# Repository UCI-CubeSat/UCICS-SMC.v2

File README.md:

# UCI CubeSat OBC v2
### Made by UCI Avionics

These design files are for the System Management Controller and Communication Subsystem of the UCI CubeSat.  
They are NOT final and are subject to change and modifications.  

Verification and finalization pending.  

Features:
- STM32F412ZG microcontroller for SMC
- 2 STM32L431RCT6 microcontrollers for communications controllers
- RF MUX and CPLD switching logic for communications failover
- AX5043 communications transceiver over SPI bus
- TCAN1042 CAN transceiver
- 4 magnetorquer PWM outputs
- 2 BMX160 interial measurement units
- CPLD error detection and handling
- 12 sun sensor ADC ports
- System and magnetorquer current monitoring via INA226 shunt resistor I2C current sensors
- External application connector

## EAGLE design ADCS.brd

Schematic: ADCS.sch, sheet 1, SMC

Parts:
C27, C28, C33, C34, C35, C36, C37, C38, C39, C40, C41, C42, C43, C44, C45, C46, C47, C48, C68, C69, C70, C71, C72, C73, C74, C75, C76, C80, C81, C82, C83, C84, C93, C94, C95, C96, C98, C99, C100, C101, C102, C103, C104, C105, C106, C107, C108, C109, C110, C111: 0.1uF; 0402
C29, C85, C86, C87, C112, C113, C114: 1uF; 0402
C88, C91, C92, C97: 2.2uF; 0402
C89, C115, C116: 4.7uF; 0603
C90, C117: 10uF; 0603
C118, C119: 10nF; 0603
C120, C121, C122, C123: 22uF; 0603
C143, C144, C145, C146, C147, C148, C149, C150, C151, C152, C153, C154, C155, C156, C172, C174: 0.1uF; 0603
C171, C173: 1uF; 0603
JP1, JP4: PINHD-1X8; 1X08
JP9: PINHD-1X4; 1X04
R3: 56R_10%; 0402
R4, R36, R38: 4.7k; 0603
R9, R40, R62, R63: 10k; 0603
R10, R12: 2.2k; 0603
R37, R39: DNI; 0603
R41: 120R; 0603
R72: 100k; 0603
U2: Value; ZWT0337A-IPC_A
U14: Value; TEXAS_INSTRUMENTS-CAN_TRANSCEIVER-TCAN1042/LED_DRIVER-TLC59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
X4: 2510-; PAK100/2500-10
Y2: 20MHz; ESC-OSCILLATOR-ECS_200_9_33B_CTP_TR

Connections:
!COMMS1_UNRESPONSIVE_FROM_SMC: R62.2, U2.F2 (GPIO20); also elsewhere on the board
!COMMS2_UNRESPONSIVE_FROM_SMC: R63.2, U2.F3 (GPIO21); also elsewhere on the board
!GLOBAL_RESET: C118.1, R4.2, U2.F19 (XRS_N); also elsewhere on the board
!MTQ_12_FAULT: U2.C11 (GPIO86); also elsewhere on the board
!MTQ_12_SLEEP: U2.B11 (GPIO85); also elsewhere on the board
!MTQ_34_FAULT: U2.D6 (GPIO89); also elsewhere on the board
!MTQ_34_SLEEP: U2.C6 (GPIO88); also elsewhere on the board
!SDRAM_CAS: U2.K4 (GPIO23); also elsewhere on the board
!SDRAM_CS: U2.U13 (GPIO32); also elsewhere on the board
!SDRAM_RAS: U2.J4 (GPIO22); also elsewhere on the board
!SDRAM_WE: U2.U11 (GPIO31); also elsewhere on the board
!SMC_NAND_CS: U2.E4 (GPIO19); also elsewhere on the board
!SMC_TRST: C119.1, R10.1, U2.V14 (TRST_N), X4.10
!TPS53513_PGOOD: R72.2; also elsewhere on the board
ADC_A0: C149.1, JP1.2, U2.U1 (ADCINA0_DACOUTA)
ADC_A1: C148.1, JP1.3, U2.T1 (ADCINA1_DACOUTB)
ADC_A2: C147.1, JP1.4, U2.U2 (ADCINA2_CMPIN1P)
ADC_A3: C146.1, JP1.5, U2.T2 (ADCINA3_CMPIN1N)
ADC_A4: C145.1, JP1.6, U2.U3 (ADCINA4_CMPIN2P)
ADC_A5: C144.1, JP1.7, U2.T3 (ADCINA5_CMPIN2N)
ADC_B0: C156.1, JP4.2, U2.V2 (ADCINB0_VDAC)
ADC_B1: C155.1, JP4.3, U2.W2 (ADCINB1_DACOUTC)
ADC_B2: C154.1, JP4.4, U2.V3 (ADCINB2_CMPIN3P)
ADC_B3: C153.1, JP4.5, U2.W3 (ADCINB3_CMPIN3N)
ADC_B4: C152.1, JP4.6, U2.V4 (ADCINB4)
ADC_B5: C151.1, JP4.7, U2.W4 (ADCINB5)
BMX160_1_INT1: U2.C1 (GPIO11); also elsewhere on the board
BMX160_1_INT2: U2.C2 (GPIO12); also elsewhere on the board
BMX160_2_INT1: U2.D1 (GPIO13); also elsewhere on the board
BMX160_2_INT2: U2.D2 (GPIO14); also elsewhere on the board
CANH: R41.1, U14.7 (CANH); also elsewhere on the board
CANL: R41.2, U14.6 (CANL); also elsewhere on the board
EPWM1A: U2.C8 (GPIO0); also elsewhere on the board
EPWM1B: U2.D8 (GPIO1); also elsewhere on the board
EPWM2A: U2.A7 (GPIO2); also elsewhere on the board
EPWM2B: U2.B7 (GPIO3); also elsewhere on the board
EPWM3A: U2.C7 (GPIO4); also elsewhere on the board
EPWM3B: U2.D7 (GPIO5); also elsewhere on the board
EPWM4A: U2.A6 (GPIO6); also elsewhere on the board
EPWM4B: U2.B6 (GPIO7); also elsewhere on the board
MAIN_CURRENT_ALERT: U2.D3 (GPIO15); also elsewhere on the board
MTQ_12_ALERT: U2.A11 (GPIO84); also elsewhere on the board
MTQ_34_ALERT: U2.D11 (GPIO87); also elsewhere on the board
unnamed: U2.J19 (X2), Y2.1 (XI)
unnamed: U2.G19 (X1), Y2.3 (XO)
unnamed: R72.1, U2.C14 (GPIO83)
SDRAM_A0: U2.T14 (GPIO35); also elsewhere on the board
SDRAM_A1: U2.V16 (GPIO36); also elsewhere on the board
SDRAM_A2: U2.U16 (GPIO37); also elsewhere on the board
SDRAM_A3: U2.T16 (GPIO38); also elsewhere on the board
SDRAM_A4: U2.W17 (GPIO39); also elsewhere on the board
SDRAM_A5: U2.K19 (GPIO45); also elsewhere on the board
SDRAM_A6: U2.E19 (GPIO46); also elsewhere on the board
SDRAM_A7: U2.E18 (GPIO47); also elsewhere on the board
SDRAM_A8: U2.R16 (GPIO48); also elsewhere on the board
SDRAM_A9: U2.R17 (GPIO49); also elsewhere on the board
SDRAM_A10: U2.R18 (GPIO50); also elsewhere on the board
SDRAM_A11: U2.R19 (GPIO51); also elsewhere on the board
SDRAM_A12: U2.P16 (GPIO52); also elsewhere on the board
SDRAM_BA0: U2.T13 (GPIO33); also elsewhere on the board
SDRAM_BA1: U2.U14 (GPIO34); also elsewhere on the board
SDRAM_CKE: U2.W11 (GPIO29); also elsewhere on the board
SDRAM_CLK: U2.T11 (GPIO30); also elsewhere on the board
SDRAM_D0: U2.P19 (GPIO55); also elsewhere on the board
SDRAM_D1: U2.N16 (GPIO56); also elsewhere on the board
SDRAM_D2: U2.N18 (GPIO57); also elsewhere on the board
SDRAM_D3: U2.N17 (GPIO58); also elsewhere on the board
SDRAM_D4: U2.M16 (GPIO59); also elsewhere on the board
SDRAM_D5: U2.M17 (GPIO60); also elsewhere on the board
SDRAM_D6: U2.L16 (GPIO61); also elsewhere on the board
SDRAM_D7: U2.J17 (GPIO62); also elsewhere on the board
SDRAM_D8: U2.C16 (GPIO76); also elsewhere on the board
SDRAM_D9: U2.D16 (GPIO75); also elsewhere on the board
SDRAM_D10: U2.C17 (GPIO74); also elsewhere on the board
SDRAM_D11: U2.A16 (GPIO73); also elsewhere on the board
SDRAM_D12: U2.B16 (GPIO72); also elsewhere on the board
SDRAM_D13: U2.B17 (GPIO71); also elsewhere on the board
SDRAM_D14: U2.A17 (GPIO70); also elsewhere on the board
SDRAM_D15: U2.B18 (GPIO69); also elsewhere on the board
SDRAM_DQM0: U2.K3 (GPIO24); also elsewhere on the board
SDRAM_DQM1: U2.K2 (GPIO25); also elsewhere on the board
SMC_ERR_OUT: R9.1, U2.U19 (ERRORSTS); also elsewhere on the board
SMC_I2C0_SCL: R37.2, U2.J3 (GPIO105); also elsewhere on the board
SMC_I2C0_SDA: R36.2, U2.J2 (GPIO104); also elsewhere on the board
SMC_I2C1_SCL: R39.2, U2.U17 (GPIO41); also elsewhere on the board
SMC_I2C1_SDA: R38.2, U2.V17 (GPIO40); also elsewhere on the board
SMC_MCAN_RX: U2.B2 (GPIO10), U14.4 (RXD)
SMC_MCAN_STB: R40.1, U2.G3 (GPIO9), U14.8 (STB)
SMC_MCAN_TX: U2.G2 (GPIO8), U14.1 (TXD)
SMC_NAND_MISO: U2.E2 (GPIO17); also elsewhere on the board
SMC_NAND_MOSI: U2.E1 (GPIO16); also elsewhere on the board
SMC_NAND_SCK: U2.E3 (GPIO18); also elsewhere on the board
SMC_TCK: U2.V15 (TCK), X4.4
SMC_TDI: U2.W13 (TDI), X4.8
SMC_TDO: U2.W15 (TDO), X4.6
SMC_TMS: R12.2, U2.W14 (TMS), X4.2
SMC_UART0_RX: JP9.3, U2.C19 (GPIO43); also elsewhere on the board
SMC_UART0_TX: JP9.2, U2.D19 (GPIO42); also elsewhere on the board
VCC_3V3_IO: C27.1, C28.1, C29.1, C33.1, C34.1, C35.1, C36.1, C37.1, C38.1, C39.1, C40.1, C41.1, C42.1, C43.1, C44.1, C45.1, C46.1, C47.1, C48.1, C68.1, C69.1, C70.1, C71.1, C72.1, C73.1, C74.1, C75.1, C76.1, C80.1, C81.1, C82.1, C83.1, C84.1, C85.1, C86.1, C87.1, C88.1, C89.1, C90.1, C91.1, C92.1, C93.1, C94.1, C95.1, C96.1, C97.1, C120.1, C121.1, C122.1, C123.1, C143.1, C150.1, C171.1, C172.1, JP1.1, JP4.1, JP9.1, R4.1, R12.1, R36.1, R37.1, R38.1, R39.1, R62.1, R63.1, U2.A9 (VDDIO_2), U2.A18 (VDDIO_3), U2.B1 (VDDIO_4), U2.E7 (VDDIO_5), U2.E10 (VDDIO_6), U2.E13 (VDDIO_7), U2.E16 (VDDIO_8), U2.F4 (VDDIO_9), U2.F7 (VDDIO_10), U2.F10 (VDDIO_11), U2.F13 (VDDIO_12), U2.F16 (VDDIO_13), U2.G4 (VDDIO_14), U2.G5 (VDDIO_15), U2.G6 (VDDIO_16), U2.H5 (VDDIO_17), U2.H6 (VDDIO_18), U2.H16 (VDDOSC_2), U2.H17 (VDDOSC), U2.L14 (VDDIO_19), U2.L15 (VDDIO_20), U2.M1 (VDDIO_21), U2.M5 (VDDIO_22), U2.M6 (VDDIO_23), U2.N14 (VDDIO_24), U2.N15 (VDDIO_25), U2.P6 (VDDA_2), U2.P9 (VDDIO_26), U2.R1 (VREFHIC), U2.R6 (VDDA), U2.R9 (VDDIO_27), U2.R11 (VDD3VFL_2), U2.R12 (VDD3VFL), U2.V1 (VREFHIA), U2.V5 (VREFHID), U2.V19 (VDDIO_28), U2.W5 (VREFHIB), U2.W8 (VDDIO), U14.5 (VIO), X4.1; also elsewhere on the board
VCC_5V0: C173.1, C174.1, U14.3 (VCC); also elsewhere on the board
VDD_CORE: C98.1, C99.1, C100.1, C101.1, C102.1, C103.1, C104.1, C105.1, C106.1, C107.1, C108.1, C109.1, C110.1, C111.1, C112.1, C113.1, C114.1, C115.1, C116.1, C117.1, R3.1, U2.E9 (VDD_2), U2.E11 (VDD_3), U2.F9 (VDD_4), U2.F11 (VDD_5), U2.G14 (VDD_6), U2.G15 (VDD_7), U2.J14 (VDD_8), U2.J15 (VDD_9), U2.K5 (VDD_10), U2.K6 (VDD_11), U2.P10 (VDD_12), U2.P13 (VDD_13), U2.R10 (VDD_14), U2.R13 (VDD)
VSS: C27.2, C28.2, C29.2, C33.2, C34.2, C35.2, C36.2, C37.2, C38.2, C39.2, C40.2, C41.2, C42.2, C43.2, C44.2, C45.2, C46.2, C47.2, C48.2, C68.2, C69.2, C70.2, C71.2, C72.2, C73.2, C74.2, C75.2, C76.2, C80.2, C81.2, C82.2, C83.2, C84.2, C85.2, C86.2, C87.2, C88.2, C89.2, C90.2, C91.2, C92.2, C93.2, C94.2, C95.2, C96.2, C97.2, C98.2, C99.2, C100.2, C101.2, C102.2, C103.2, C104.2, C105.2, C106.2, C107.2, C108.2, C109.2, C110.2, C111.2, C112.2, C113.2, C114.2, C115.2, C116.2, C117.2, C118.2, C119.2, C120.2, C121.2, C122.2, C123.2, C143.2, C144.2, C145.2, C146.2, C147.2, C148.2, C149.2, C150.2, C151.2, C152.2, C153.2, C154.2, C155.2, C156.2, C171.2, C172.2, C173.2, C174.2, JP1.8, JP4.8, JP9.4, R3.2, R9.2, R10.2, R40.2, U2.A1 (VSS_2), U2.A10 (VSS_3), U2.A19 (VSS_4), U2.E5 (VSS_5), U2.E6 (VSS_6), U2.E8 (VSS_7), U2.E12 (VSS_8), U2.E14 (VSS_9), U2.E15 (VSS_10), U2.F5 (VSS_11), U2.F6 (VSS_12), U2.F8 (VSS_13), U2.F12 (VSS_14), U2.F14 (VSS_15), U2.F15 (VSS_16), U2.G16 (VSS_17), U2.G17 (VSS_18), U2.H8 (VSS_19), U2.H9 (VSS_20), U2.H10 (VSS_21), U2.H11 (VSS_22), U2.H12 (VSS_23), U2.H14 (VSS_24), U2.H15 (VSS_25), U2.H18 (VSSOSC_2), U2.H19 (VSSOSC), U2.J5 (VSS_26), U2.J6 (VSS_27), U2.J8 (VSS_28), U2.J9 (VSS_29), U2.J10 (VSS_30), U2.J11 (VSS_31), U2.J12 (VSS_32), U2.K8 (VSS_33), U2.K9 (VSS_34), U2.K10 (VSS_35), U2.K11 (VSS_36), U2.K12 (VSS_37), U2.K14 (VSS_38), U2.K15 (VSS_39), U2.L5 (VSS_40), U2.L6 (VSS_41), U2.L8 (VSS_42), U2.L9 (VSS_43), U2.L10 (VSS_44), U2.L11 (VSS_45), U2.L12 (VSS_46), U2.L18 (VSS_47), U2.M8 (VSS_48), U2.M9 (VSS_49), U2.M10 (VSS_50), U2.M11 (VSS_51), U2.M12 (VSS_52), U2.M14 (VSS_53), U2.M15 (VSS_54), U2.N1 (VSS_55), U2.N5 (VSS_56), U2.N6 (VSS_57), U2.P1 (VSSA_2), U2.P2 (VREFLOC), U2.P5 (VSSA_3), U2.P7 (VSS_58), U2.P8 (VSS_59), U2.P11 (VSS_60), U2.P12 (VSS_61), U2.P14 (VSS_62), U2.P15 (VSS_63), U2.R2 (VREFLOA), U2.R5 (VSSA_4), U2.R7 (VSS_64), U2.R8 (VSS_65), U2.R14 (VSS_66), U2.R15 (VSS_67), U2.V6 (VREFLOB), U2.V7 (VSSA_5), U2.W1 (VSSA), U2.W6 (VREFLOD), U2.W7 (VSS_68), U2.W19 (VSS), U14.2 (GND), X4.3, X4.5, X4.9, Y2.2 (VSS), Y2.4 (VSS); also elsewhere on the board

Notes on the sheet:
Ground block
VDD + Decaps
ADC block (sun sensor and auxiliary)
SMC control block

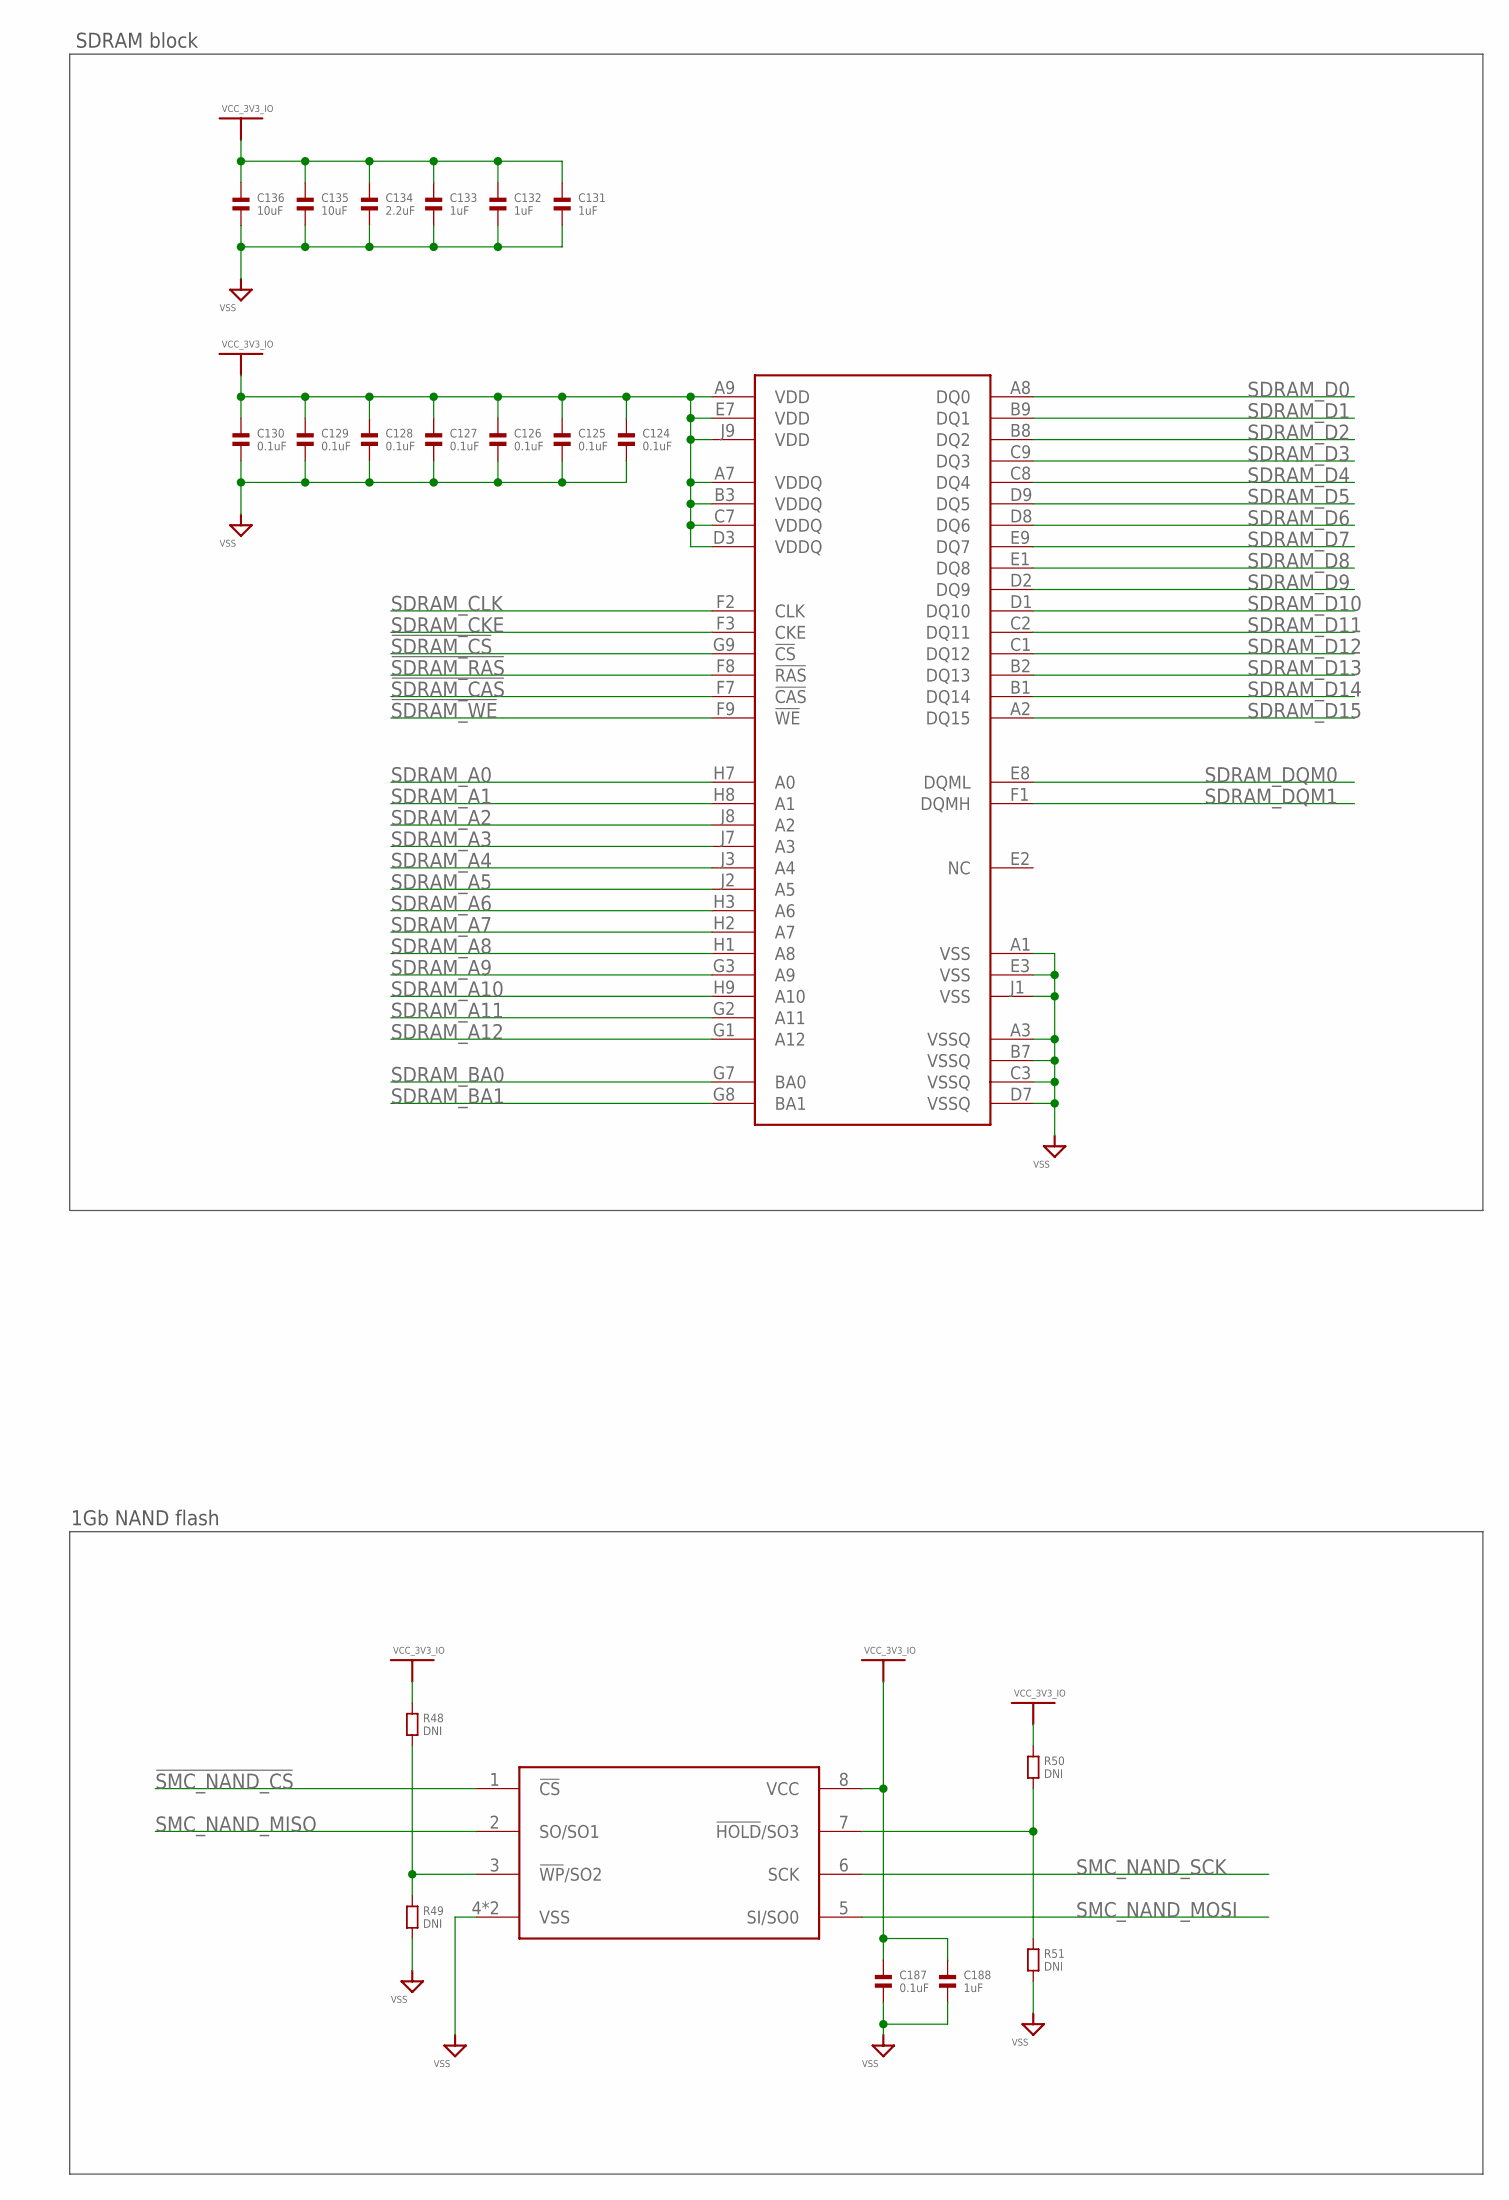
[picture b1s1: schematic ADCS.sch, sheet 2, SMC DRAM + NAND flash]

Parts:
C124, C125, C126, C127, C128, C129, C130, C187: 0.1uF; 0603
C131, C132, C133, C188: 1uF; 0603
C134: 2.2uF; 0603
C135, C136: 10uF; 0603
R48, R49, R50, R51: DNI; 0603
U6: ISSI-DRAM-IS42S16320F-7TL
U16: KIOXIA_AMERICA-NAND_FLASH-TC58CVG0S3HRAIG

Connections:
!SDRAM_CAS: U6.F7 (!CAS); also elsewhere on the board
!SDRAM_CS: U6.G9 (!CS); also elsewhere on the board
!SDRAM_RAS: U6.F8 (!RAS); also elsewhere on the board
!SDRAM_WE: U6.F9 (!WE); also elsewhere on the board
!SMC_NAND_CS: U16.1 (!CS); also elsewhere on the board
unnamed: R48.2, R49.1, U16.3 (!WP!/SO2)
unnamed: R50.2, R51.1, U16.7 (!HOLD!/SO3)
SDRAM_A0: U6.H7 (A0); also elsewhere on the board
SDRAM_A1: U6.H8 (A1); also elsewhere on the board
SDRAM_A2: U6.J8 (A2); also elsewhere on the board
SDRAM_A3: U6.J7 (A3); also elsewhere on the board
SDRAM_A4: U6.J3 (A4); also elsewhere on the board
SDRAM_A5: U6.J2 (A5); also elsewhere on the board
SDRAM_A6: U6.H3 (A6); also elsewhere on the board
SDRAM_A7: U6.H2 (A7); also elsewhere on the board
SDRAM_A8: U6.H1 (A8); also elsewhere on the board
SDRAM_A9: U6.G3 (A9); also elsewhere on the board
SDRAM_A10: U6.H9 (A10); also elsewhere on the board
SDRAM_A11: U6.G2 (A11); also elsewhere on the board
SDRAM_A12: U6.G1 (A12); also elsewhere on the board
SDRAM_BA0: U6.G7 (BA0); also elsewhere on the board
SDRAM_BA1: U6.G8 (BA1); also elsewhere on the board
SDRAM_CKE: U6.F3 (CKE); also elsewhere on the board
SDRAM_CLK: U6.F2 (CLK); also elsewhere on the board
SDRAM_D0: U6.A8 (DQ0); also elsewhere on the board
SDRAM_D1: U6.B9 (DQ1); also elsewhere on the board
SDRAM_D2: U6.B8 (DQ2); also elsewhere on the board
SDRAM_D3: U6.C9 (DQ3); also elsewhere on the board
SDRAM_D4: U6.C8 (DQ4); also elsewhere on the board
SDRAM_D5: U6.D9 (DQ5); also elsewhere on the board
SDRAM_D6: U6.D8 (DQ6); also elsewhere on the board
SDRAM_D7: U6.E9 (DQ7); also elsewhere on the board
SDRAM_D8: U6.E1 (DQ8); also elsewhere on the board
SDRAM_D9: U6.D2 (DQ9); also elsewhere on the board
SDRAM_D10: U6.D1 (DQ10); also elsewhere on the board
SDRAM_D11: U6.C2 (DQ11); also elsewhere on the board
SDRAM_D12: U6.C1 (DQ12); also elsewhere on the board
SDRAM_D13: U6.B2 (DQ13); also elsewhere on the board
SDRAM_D14: U6.B1 (DQ14); also elsewhere on the board
SDRAM_D15: U6.A2 (DQ15); also elsewhere on the board
SDRAM_DQM0: U6.E8 (DQML); also elsewhere on the board
SDRAM_DQM1: U6.F1 (DQMH); also elsewhere on the board
SMC_NAND_MISO: U16.2 (SO/SO1); also elsewhere on the board
SMC_NAND_MOSI: U16.5 (SI/SO0); also elsewhere on the board
SMC_NAND_SCK: U16.6 (SCK); also elsewhere on the board
VCC_3V3_IO: C124.1, C125.1, C126.1, C127.1, C128.1, C129.1, C130.1, C131.1, C132.1, C133.1, C134.1, C135.1, C136.1, C187.1, C188.1, R48.1, R50.1, U6.A7 (VDDQ), U6.A9 (VDD), U6.B3 (VDDQ), U6.C7 (VDDQ), U6.D3 (VDDQ), U6.E7 (VDD), U6.J9 (VDD), U16.8 (VCC); also elsewhere on the board
VSS: C124.2, C125.2, C126.2, C127.2, C128.2, C129.2, C130.2, C131.2, C132.2, C133.2, C134.2, C135.2, C136.2, C187.2, C188.2, R49.2, R51.2, U6.A1 (VSS), U6.A3 (VSSQ), U6.B7 (VSSQ), U6.C3 (VSSQ), U6.D7 (VSSQ), U6.E3 (VSS), U6.J1 (VSS), U16.4 (VSS), U16.9 (VSS); also elsewhere on the board

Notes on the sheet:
SDRAM block
1Gb NAND flash

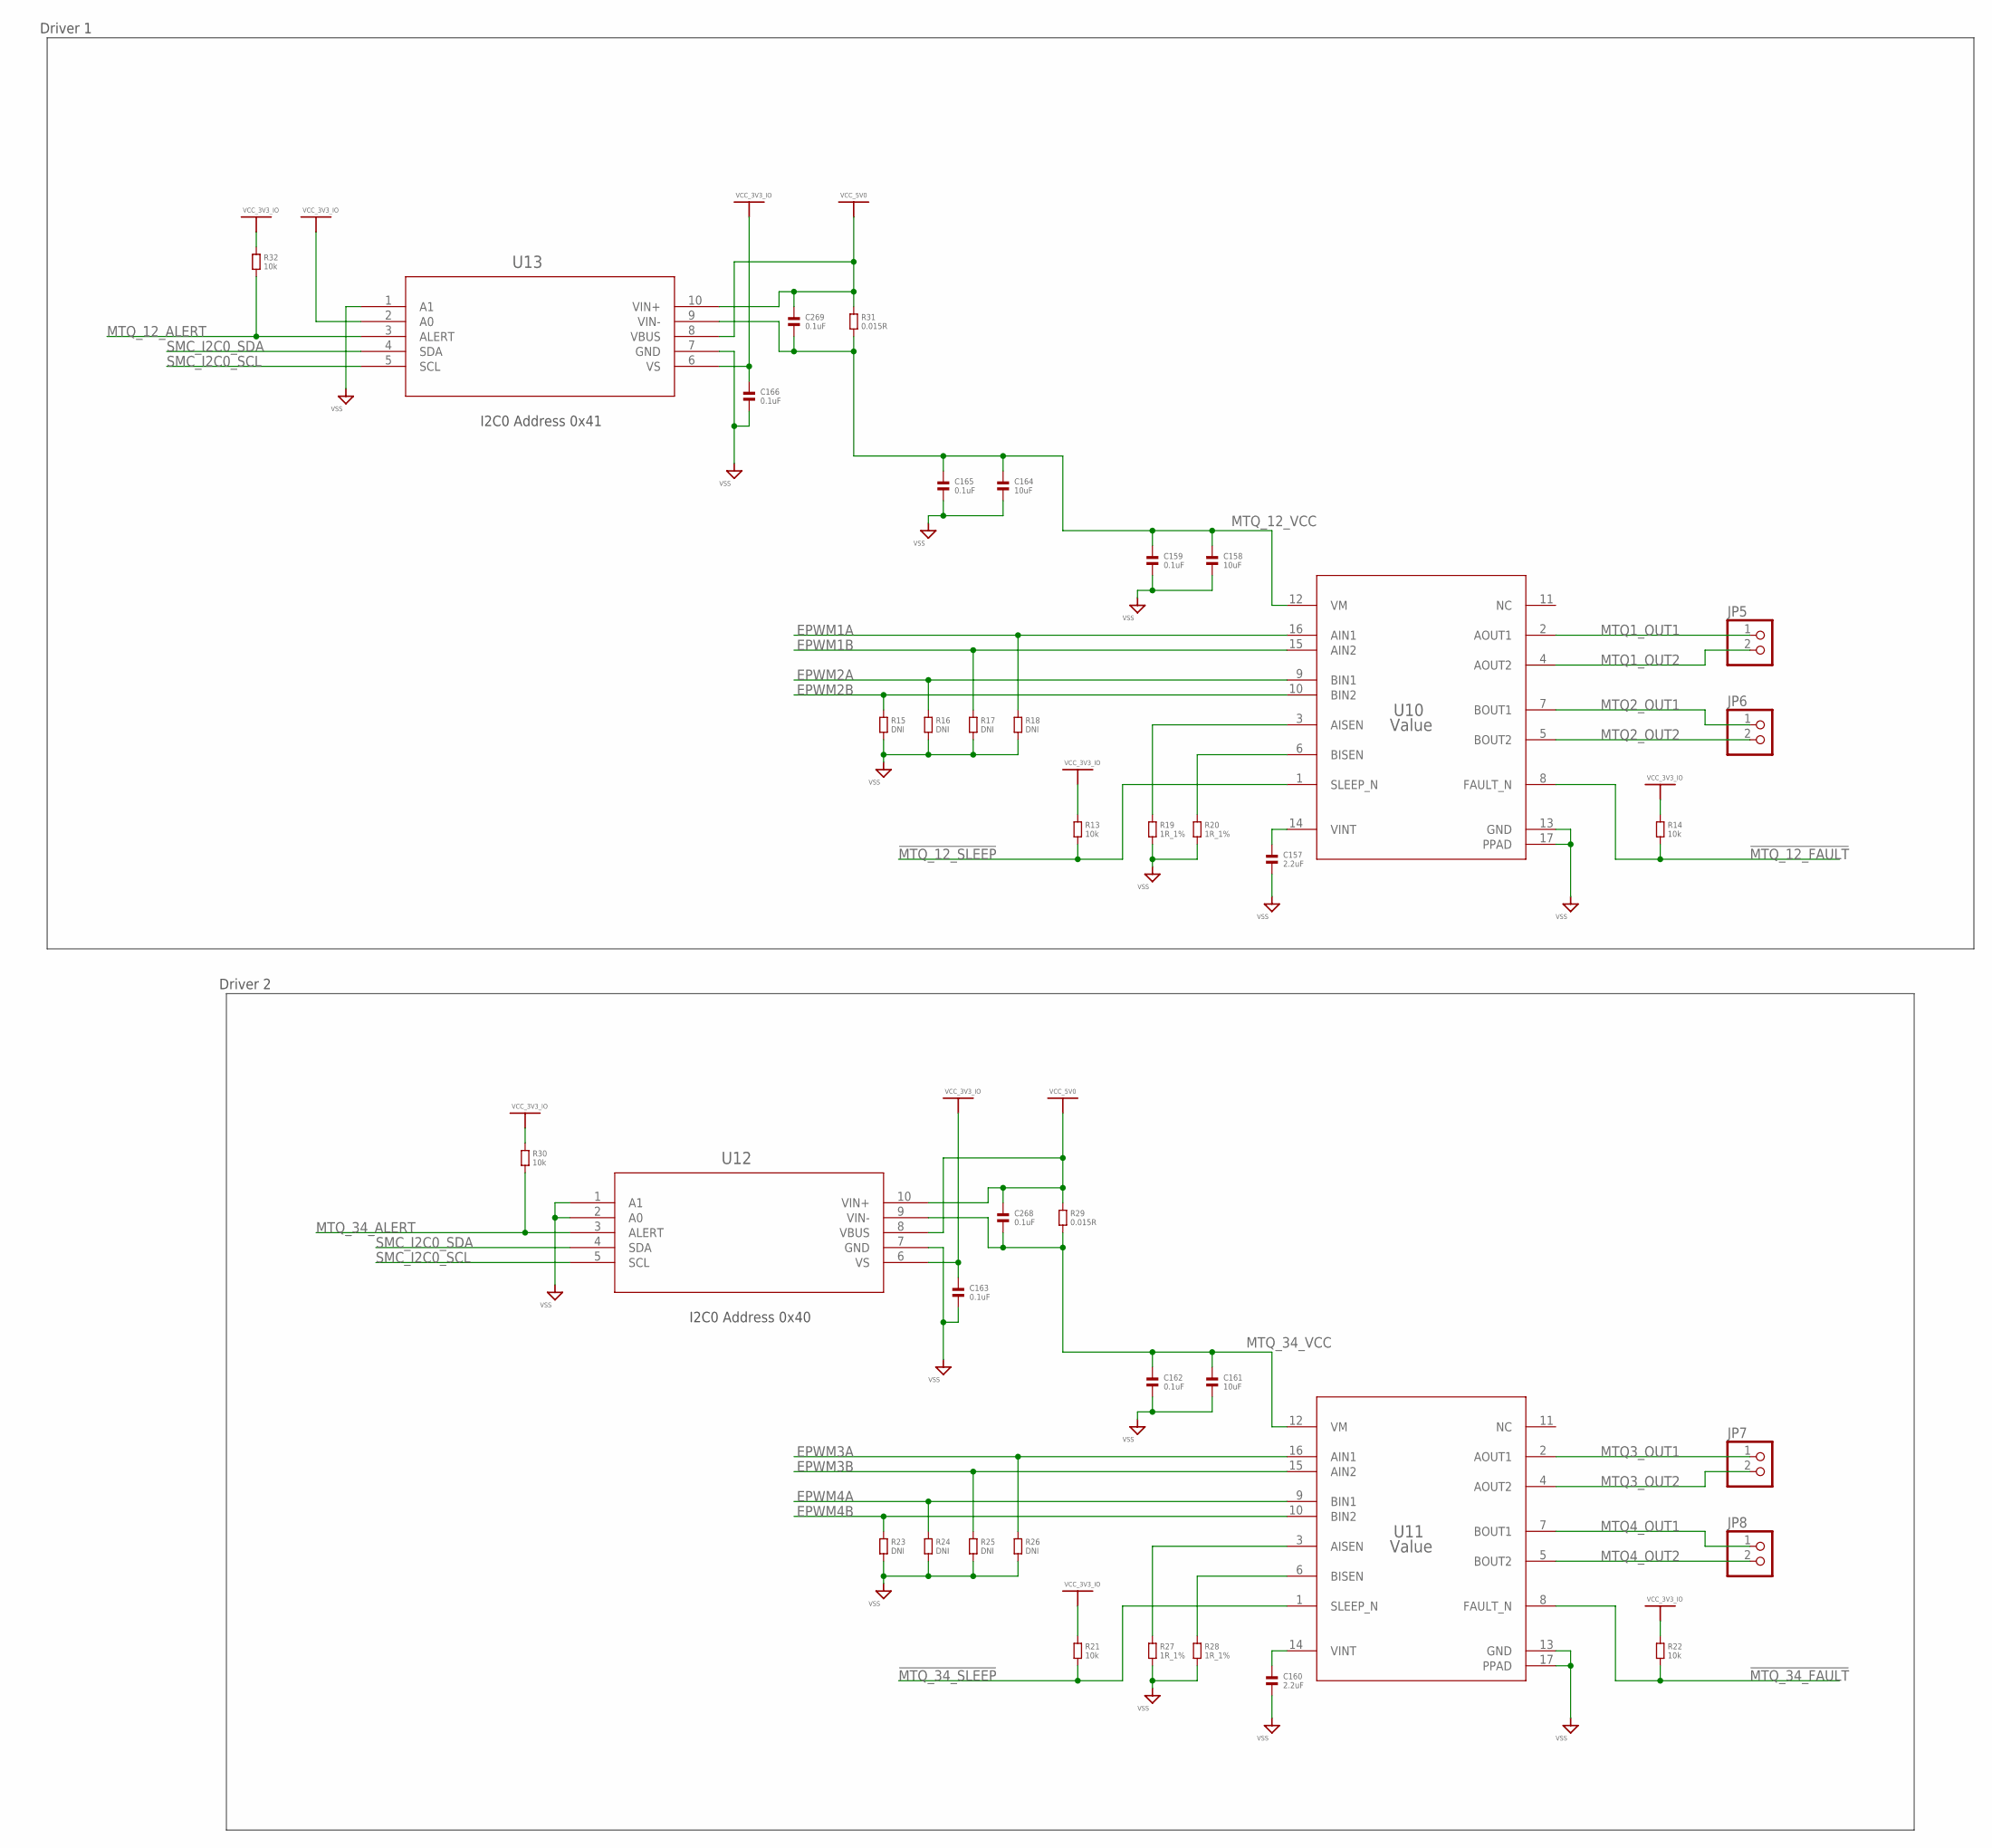
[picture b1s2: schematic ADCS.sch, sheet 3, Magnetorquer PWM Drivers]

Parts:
C157, C160: 2.2uF; 0603
C158, C161, C164: 10uF; 0805
C159, C162, C163, C165, C166, C268, C269: 0.1uF; 0603
JP5, JP6, JP7, JP8: PINHD-1X2; 1X02
R13, R14, R21, R22, R30, R32: 10k; 0603
R15, R16, R17, R18, R23, R24, R25, R26: DNI; 0603
R19, R20, R27, R28: 1R_1%; 0603
R29, R31: 0.015R; 1206
U10, U11: Value; PWP0016K_N
U12, U13: TEXAS_INSTRUMENTS-CURRENT_MONITOR-INA226_DGS_10

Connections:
!MTQ_12_FAULT: R14.2, U10.8 (FAULT_N); also elsewhere on the board
!MTQ_12_SLEEP: R13.2, U10.1 (SLEEP_N); also elsewhere on the board
!MTQ_34_FAULT: R22.2, U11.8 (FAULT_N); also elsewhere on the board
!MTQ_34_SLEEP: R21.2, U11.1 (SLEEP_N); also elsewhere on the board
EPWM1A: R18.1, U10.16 (AIN1); also elsewhere on the board
EPWM1B: R17.1, U10.15 (AIN2); also elsewhere on the board
EPWM2A: R16.1, U10.9 (BIN1); also elsewhere on the board
EPWM2B: R15.1, U10.10 (BIN2); also elsewhere on the board
EPWM3A: R26.1, U11.16 (AIN1); also elsewhere on the board
EPWM3B: R25.1, U11.15 (AIN2); also elsewhere on the board
EPWM4A: R24.1, U11.9 (BIN1); also elsewhere on the board
EPWM4B: R23.1, U11.10 (BIN2); also elsewhere on the board
MTQ1_OUT1: JP5.1, U10.2 (AOUT1)
MTQ1_OUT2: JP5.2, U10.4 (AOUT2)
MTQ2_OUT1: JP6.1, U10.7 (BOUT1)
MTQ2_OUT2: JP6.2, U10.5 (BOUT2)
MTQ3_OUT1: JP7.1, U11.2 (AOUT1)
MTQ3_OUT2: JP7.2, U11.4 (AOUT2)
MTQ4_OUT1: JP8.1, U11.7 (BOUT1)
MTQ4_OUT2: JP8.2, U11.5 (BOUT2)
MTQ_12_ALERT: R32.2, U13.3 (ALERT); also elsewhere on the board
MTQ_12_VCC: C158.1, C159.1, C164.1, C165.1, C269.2, R31.2, U10.12 (VM), U13.9 (VIN-)
MTQ_34_ALERT: R30.2, U12.3 (ALERT); also elsewhere on the board
MTQ_34_VCC: C161.1, C162.1, C268.2, R29.2, U11.12 (VM), U12.9 (VIN-)
unnamed: C157.1, U10.14 (VINT)
unnamed: R19.1, U10.3 (AISEN)
unnamed: R20.1, U10.6 (BISEN)
unnamed: C160.1, U11.14 (VINT)
unnamed: R27.1, U11.3 (AISEN)
unnamed: R28.1, U11.6 (BISEN)
SMC_I2C0_SCL: U12.5 (SCL), U13.5 (SCL); also elsewhere on the board
SMC_I2C0_SDA: U12.4 (SDA), U13.4 (SDA); also elsewhere on the board
VCC_3V3_IO: C163.1, C166.1, R13.1, R14.1, R21.1, R22.1, R30.1, R32.1, U12.6 (VS), U13.2 (A0), U13.6 (VS); also elsewhere on the board
VCC_5V0: C268.1, C269.1, R29.1, R31.1, U12.8 (VBUS), U12.10 (VIN+), U13.8 (VBUS), U13.10 (VIN+); also elsewhere on the board
VSS: C157.2, C158.2, C159.2, C160.2, C161.2, C162.2, C163.2, C164.2, C165.2, C166.2, R15.2, R16.2, R17.2, R18.2, R19.2, R20.2, R23.2, R24.2, R25.2, R26.2, R27.2, R28.2, U10.13 (GND), U10.17 (PPAD), U11.13 (GND), U11.17 (PPAD), U12.1 (A1), U12.2 (A0), U12.7 (GND), U13.1 (A1), U13.7 (GND); also elsewhere on the board

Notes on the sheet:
I2C0 Address 0x40
I2C0 Address 0x41
Driver 2
Driver 1

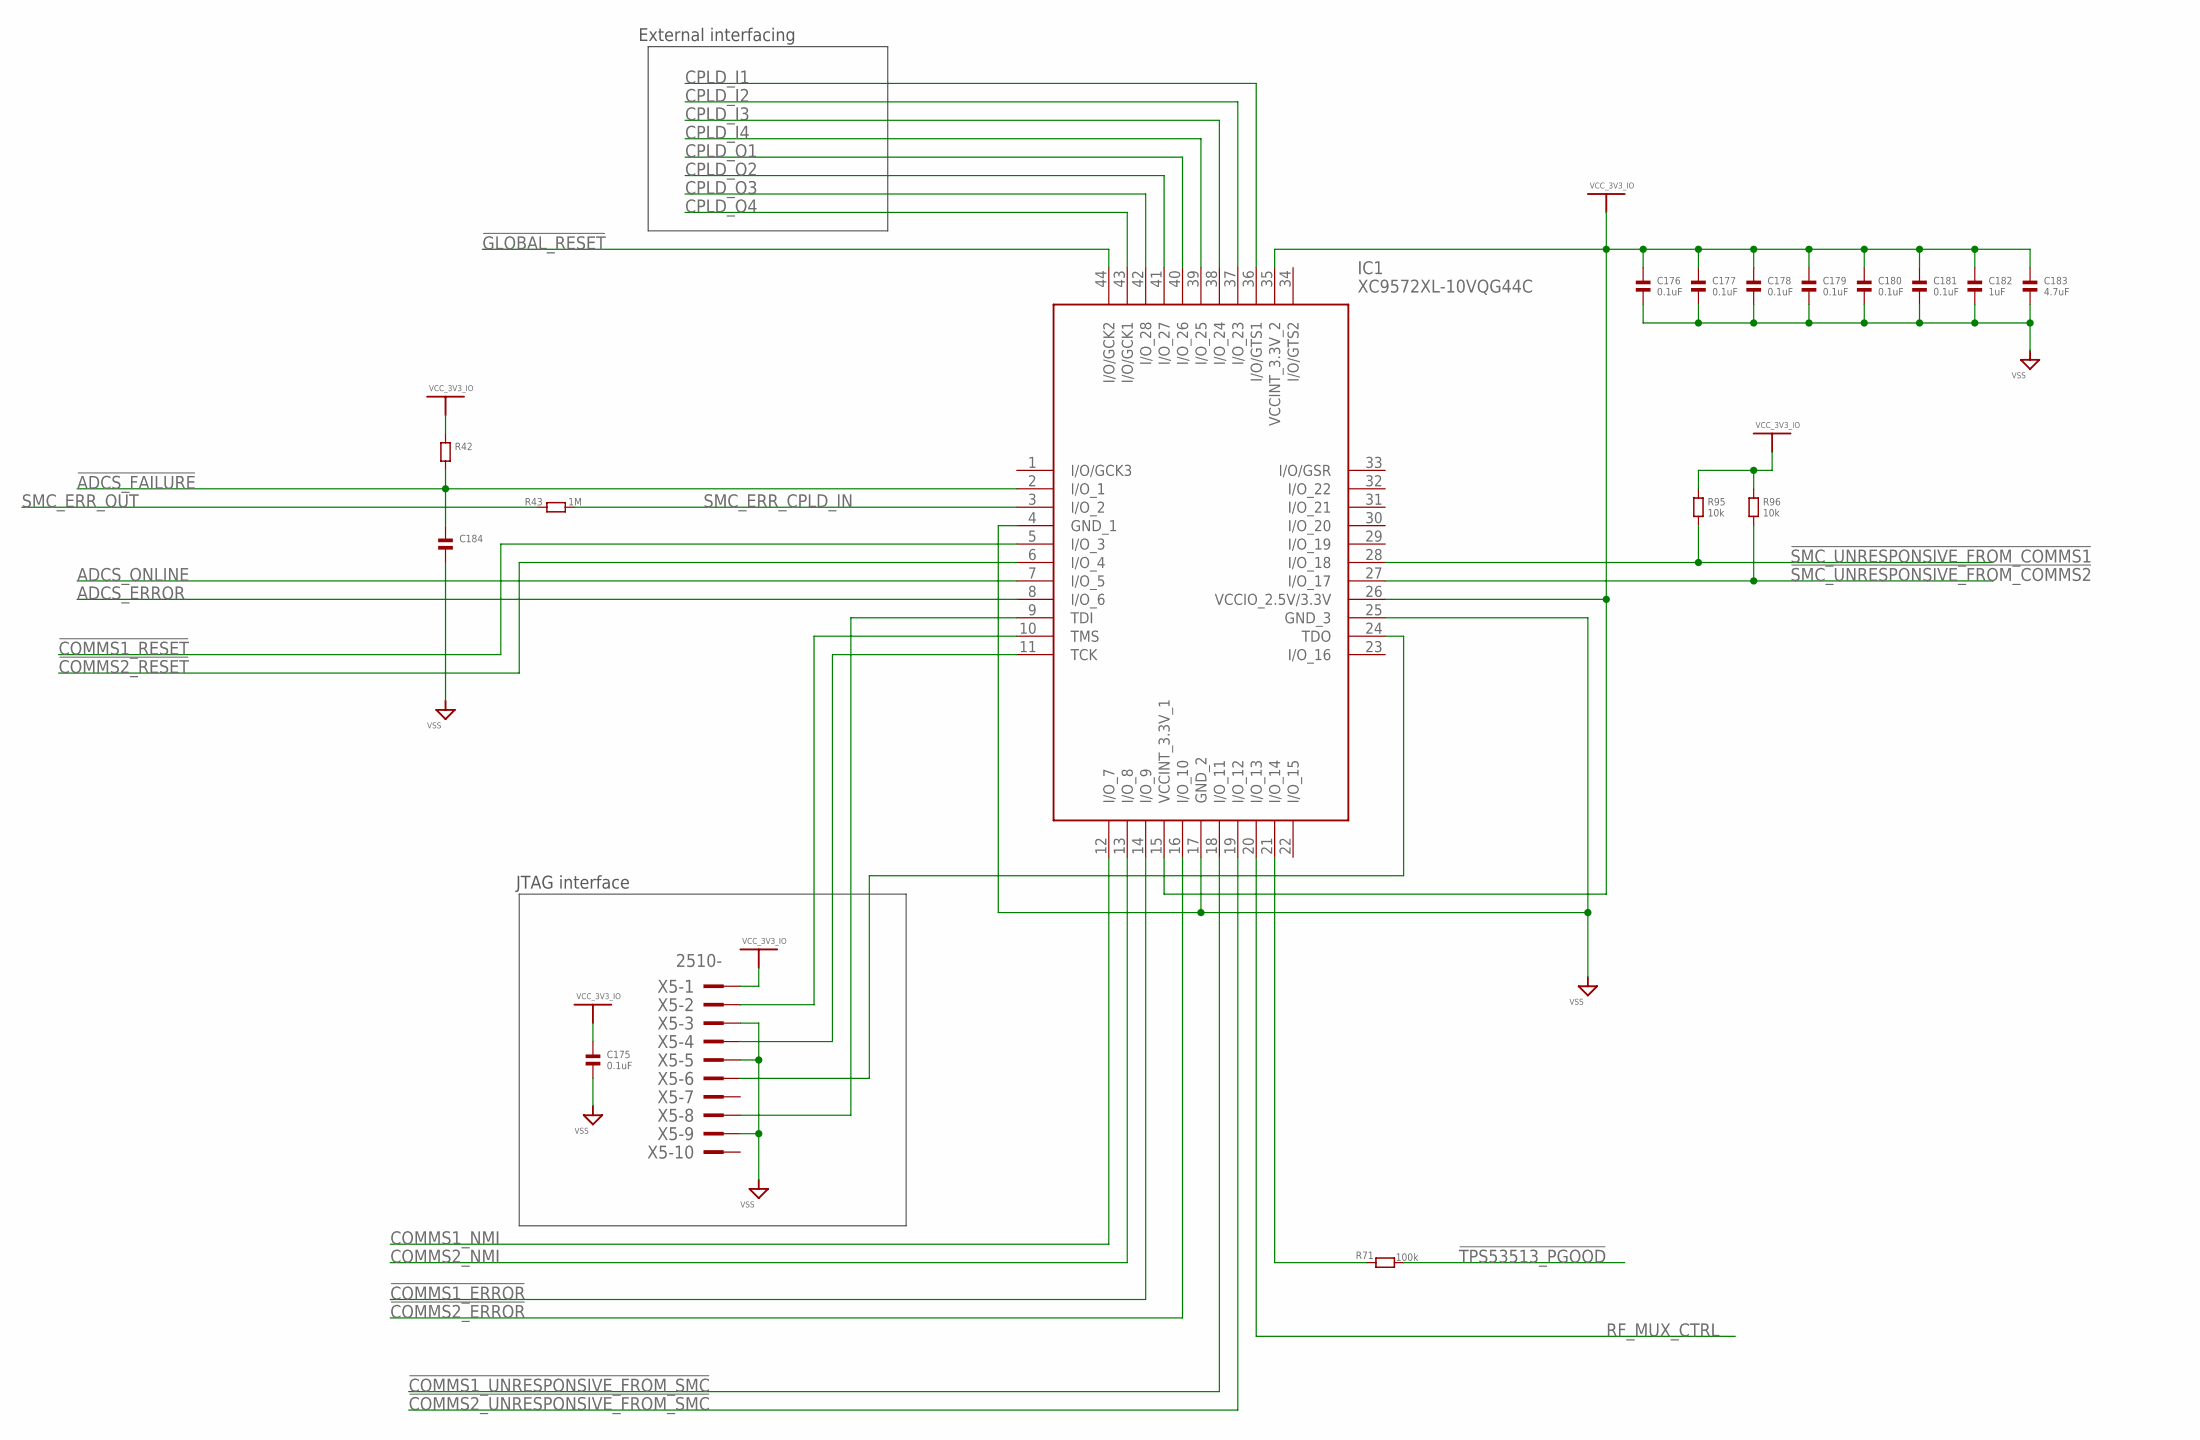
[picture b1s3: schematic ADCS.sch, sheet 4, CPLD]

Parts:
C175, C176, C177, C178, C179, C180, C181: 0.1uF; 0603
C182: 1uF; 0603
C183: 4.7uF; 0603
C184: CAPACITOR.0603; 0603
IC1: XC9572XL-10VQG44C; QFP80P1200X1200X120-44N
R42: RESISTOR.0603; 0603
R43: 1M; 0603
R71: 100k; 0603
R95, R96: 10k; 0603
X5: 2510-; PAK100/2500-10

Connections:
!ADCS_FAILURE: C184.1, IC1.2 (I/O_1), R42.2
!COMMS1_ERROR: IC1.14 (I/O_9); also elsewhere on the board
!COMMS1_RESET: IC1.5 (I/O_3); also elsewhere on the board
!COMMS1_UNRESPONSIVE_FROM_SMC: IC1.18 (I/O_11); also elsewhere on the board
!COMMS2_ERROR: IC1.16 (I/O_10); also elsewhere on the board
!COMMS2_RESET: IC1.6 (I/O_4); also elsewhere on the board
!COMMS2_UNRESPONSIVE_FROM_SMC: IC1.19 (I/O_12); also elsewhere on the board
!GLOBAL_RESET: IC1.44 (I/O/GCK2); also elsewhere on the board
!SMC_UNRESPONSIVE_FROM_COMMS1: IC1.28 (I/O_18), R95.2; also elsewhere on the board
!SMC_UNRESPONSIVE_FROM_COMMS2: IC1.27 (I/O_17), R96.2; also elsewhere on the board
!TPS53513_PGOOD: R71.2; also elsewhere on the board
ADCS_ERROR: IC1.8 (I/O_6); also elsewhere on the board
ADCS_ONLINE: IC1.7 (I/O_5); also elsewhere on the board
COMMS1_NMI: IC1.12 (I/O_7); also elsewhere on the board
COMMS2_NMI: IC1.13 (I/O_8); also elsewhere on the board
CPLD_I1: IC1.36 (I/O/GTS1); also elsewhere on the board
CPLD_I2: IC1.37 (I/O_23); also elsewhere on the board
CPLD_I3: IC1.38 (I/O_24); also elsewhere on the board
CPLD_I4: IC1.39 (I/O_25); also elsewhere on the board
CPLD_O1: IC1.40 (I/O_26); also elsewhere on the board
CPLD_O2: IC1.41 (I/O_27); also elsewhere on the board
CPLD_O3: IC1.42 (I/O_28); also elsewhere on the board
CPLD_O4: IC1.43 (I/O/GCK1); also elsewhere on the board
unnamed: IC1.10 (TMS), X5.2
unnamed: IC1.11 (TCK), X5.4
unnamed: IC1.9 (TDI), X5.8
unnamed: IC1.24 (TDO), X5.6
unnamed: IC1.21 (I/O_14), R71.1
RF_MUX_CTRL: IC1.20 (I/O_13); also elsewhere on the board
SMC_ERR_CPLD_IN: IC1.3 (I/O_2), R43.2
SMC_ERR_OUT: R43.1; also elsewhere on the board
VCC_3V3_IO: C175.1, C176.1, C177.1, C178.1, C179.1, C180.1, C181.1, C182.1, C183.1, IC1.15 (VCCINT_3.3V_1), IC1.26 (VCCIO_2.5V/3.3V), IC1.35 (VCCINT_3.3V_2), R42.1, R95.1, R96.1, X5.1; also elsewhere on the board
VSS: C175.2, C176.2, C177.2, C178.2, C179.2, C180.2, C181.2, C182.2, C183.2, C184.2, IC1.4 (GND_1), IC1.17 (GND_2), IC1.25 (GND_3), X5.3, X5.5, X5.9; also elsewhere on the board

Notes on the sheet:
JTAG interface
External interfacing

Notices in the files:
parts and their libraries:
COPYRIGHT: Copyright (C) 2018 Accelerated Designs. All rights reserved
